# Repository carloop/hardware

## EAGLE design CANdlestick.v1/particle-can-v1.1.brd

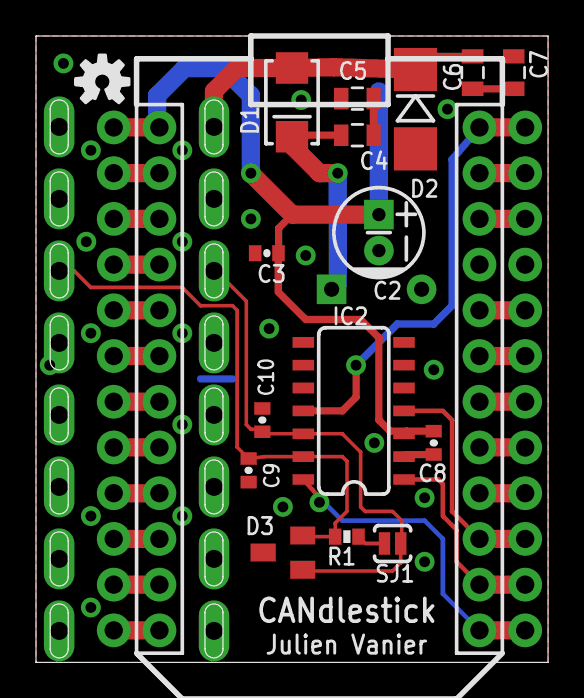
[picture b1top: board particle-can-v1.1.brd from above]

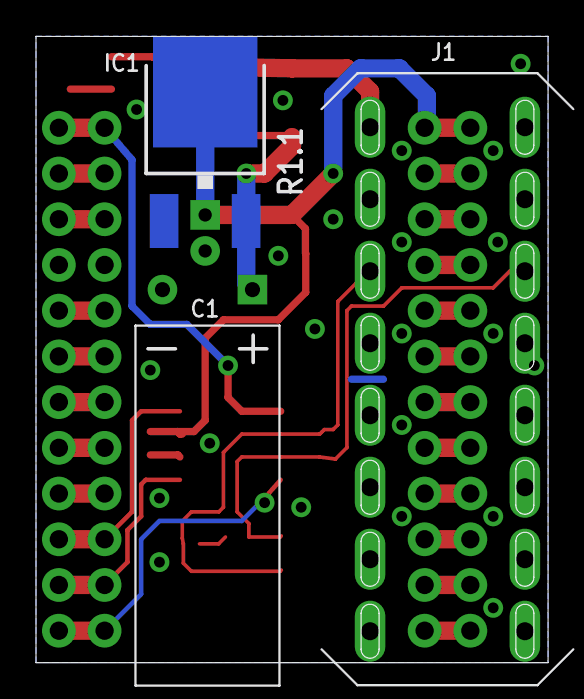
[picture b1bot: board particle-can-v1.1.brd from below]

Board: 2 copper layers, 28.4 x 34.8 mm, 22 parts (3 on the bottom side), 30 nets.

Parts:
C1: 270u; CPOL-8MMX20MM-FLAT
C2: 150u; CPOL-5MMX2D
C3: 22n; 0402-CAP
C4, C5: 0.1u; 0805
C6, C7: 0.47u; 0805
C8: 0.1u; 0402-CAP
C9, C10: 100p; 0402-CAP
CORE: SPARK_COREOUTSIDE; SPARK_CORE_OUTSIDE
D1: RS1J; SMA-DIODE
D2: 1SMB16CAT3G; SMB-DIODE
D3: PESD1CAN; SOT23
DRILEGEND: DRILEGEND
F2: OSHW-LOGO-S
IC1: LM340S-50; V-REG_DPACK
IC2: TJA1048T; SO14
J1: OBDII; OBDII-STRAIGHT
R1: 120; 0402-RES
SJ1: OPEN; SJ_2S-NO
ZDRAW1: A4L-LOC

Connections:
3.3V: CORE.24, CORE.@24, IC2.11
5V: C2.1, C3.1, C8.2, CORE.1, CORE.@1, IC1.4, IC2.3
+12V: C6.1, D1.A, D2.C, J1.16
CANA_EN: CORE.13, CORE.@13, IC2.14
CANA_RX: CORE.15, CORE.@15, IC2.4
CANA_TX: CORE.14, CORE.@14, IC2.1
GND: C1.1, C2.2, C3.2, C5.2, C7.2, C8.1, C9.2, C10.2, CORE.2, CORE.21, CORE.@2, CORE.@21, D2.A, D3.3, IC1.1, IC2.2, IC2.5, J1.4, J1.5
HSPD_HI: C9.1, D3.2, IC2.13, J1.6, R1.1
HSPD_LO: C10.1, D3.1, IC2.12, J1.14, SJ1.1
unnamed: R1.2, SJ1.2
unnamed: C6.2, C7.1
unnamed: CORE.23, CORE.@23
unnamed: CORE.22, CORE.@22
unnamed: CORE.20, CORE.@20
unnamed: CORE.19, CORE.@19
unnamed: CORE.18, CORE.@18
unnamed: CORE.17, CORE.@17
unnamed: CORE.16, CORE.@16
unnamed: CORE.12, CORE.@12
unnamed: CORE.11, CORE.@11
unnamed: CORE.10, CORE.@10
unnamed: CORE.9, CORE.@9
unnamed: C4.2, C5.1
unnamed: C1.2, C4.1, D1.C, IC1.3
unnamed: CORE.8, CORE.@8
unnamed: CORE.7, CORE.@7
unnamed: CORE.6, CORE.@6
unnamed: CORE.5, CORE.@5
unnamed: CORE.4, CORE.@4
unnamed: CORE.3, CORE.@3

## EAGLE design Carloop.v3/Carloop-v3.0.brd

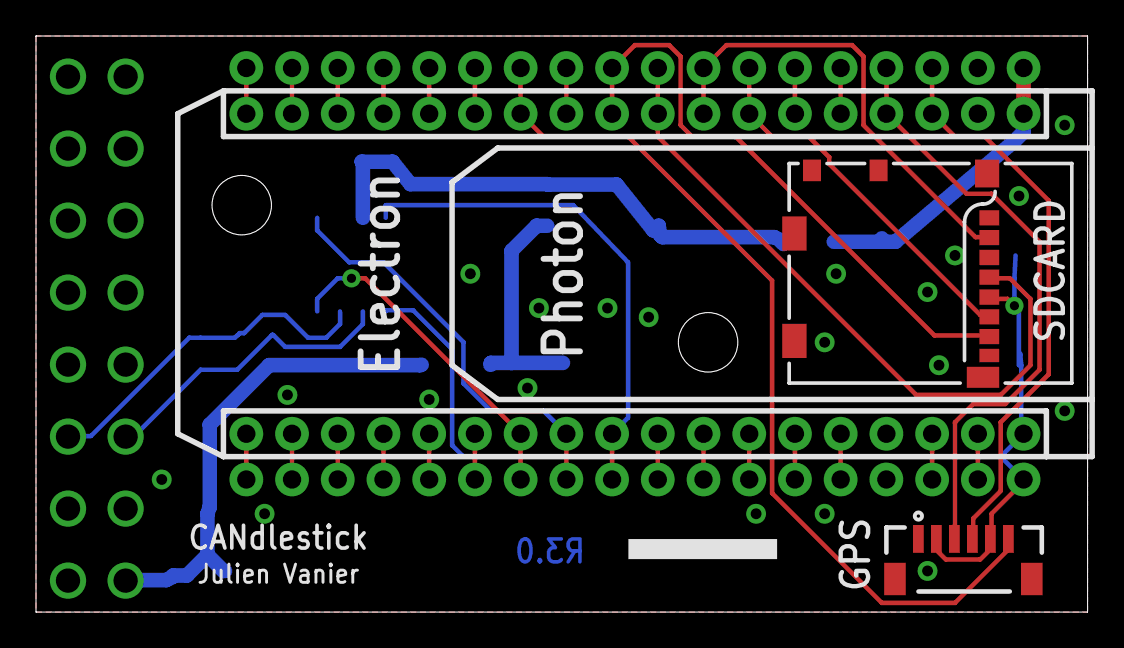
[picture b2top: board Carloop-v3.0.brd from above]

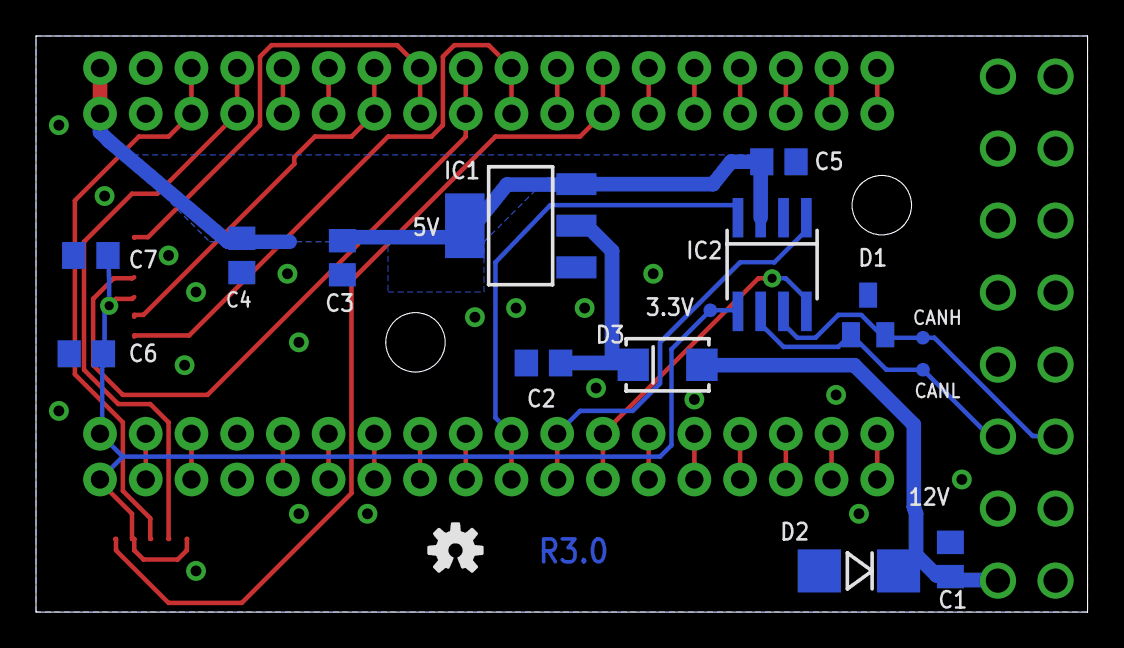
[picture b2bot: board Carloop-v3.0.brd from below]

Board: 2 copper layers, 58.4 x 32.0 mm, 24 parts (17 on the bottom side), 39 nets.

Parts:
C1: .47u; C0805
C2: 10u; C0805
C3: 22u; C0805
C4: DNP; C0805
C5, C6: 0.1u; C0805
C7: 1u; C0805
D1: PESD1CAN; SOT23
D2: 1SMB16CAT3G; SMB-DIODE
D3: RS1J; SMA-DIODE
ELECTRON: ELECTRON_WITH_EXTERNAL_HEADERS; ELECTRON_EXTERNAL
F2: OSHW-LOGO-S
GPS: JST; JST-6-SMD-VERT-1.0MM
IC1: NCP1117; SOT223
IC2: TJA1049; SO8
J1: OBDII; OBDII-COMTECH
SDCARD: USD-SOCKETMOLEX; MICRO-SD-MOLEX
STANDOFF1, STANDOFF2: STAND-OFF
TP1: CANH; PAD.03X.03
TP2: CANL; PAD.03X.03
TP3: 12V; PAD.03X.03
TP5: 3.3V; PAD.03X.03
ZDRAW1: A4L-LOC

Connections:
3.3V: C6.1, C7.1, ELECTRON.36, ELECTRON.@36, GPS.2, GPS.5, IC2.5, SDCARD.4, TP5.P$1
5V: C3.1, C4.1, C5.2, ELECTRON.1, ELECTRON.@1, IC1.3, IC1.4, IC2.3
+12V: C1.1, D2.C, D3.A, J1.16, TP3.P$1
CANA_EN: ELECTRON.25, ELECTRON.@25, IC2.8
CANA_RX: ELECTRON.27, ELECTRON.@27, IC2.4
CANA_TX: ELECTRON.26, ELECTRON.@26, IC2.1
GND: C1.2, C2.2, C3.2, C4.2, C5.1, C6.2, C7.2, D1.3, D2.A, ELECTRON.2, ELECTRON.33, ELECTRON.@2, ELECTRON.@33, GPS.1, IC1.1, IC2.2, J1.4, J1.5, SDCARD.6, SDCARD.CD1, SDCARD.CD2, SDCARD.G1, SDCARD.G2, SDCARD.G3, SDCARD.G4
GPS_EN: ELECTRON.12, ELECTRON.@12, GPS.6
GPS_RX: ELECTRON.3, ELECTRON.@3, GPS.4
GPS_TX: ELECTRON.4, ELECTRON.@4, GPS.3
HSPD_HI: D1.2, IC2.7, J1.6, TP1.P$1
HSPD_LO: D1.1, IC2.6, J1.14, TP2.P$1
unnamed: ELECTRON.13, ELECTRON.@13
unnamed: ELECTRON.14, ELECTRON.@14
unnamed: ELECTRON.35, ELECTRON.@35
unnamed: ELECTRON.34, ELECTRON.@34
unnamed: ELECTRON.32, ELECTRON.@32
unnamed: ELECTRON.31, ELECTRON.@31
unnamed: ELECTRON.30, ELECTRON.@30
unnamed: ELECTRON.29, ELECTRON.@29
unnamed: ELECTRON.28, ELECTRON.@28
unnamed: ELECTRON.15, ELECTRON.@15
unnamed: ELECTRON.11, ELECTRON.@11
unnamed: ELECTRON.16, ELECTRON.@16
unnamed: ELECTRON.17, ELECTRON.@17
unnamed: ELECTRON.18, ELECTRON.@18
unnamed: ELECTRON.19, ELECTRON.@19
unnamed: ELECTRON.20, ELECTRON.@20
unnamed: ELECTRON.21, ELECTRON.@21
unnamed: ELECTRON.6, ELECTRON.@6
unnamed: ELECTRON.5, ELECTRON.@5
unnamed: ELECTRON.23, ELECTRON.@23
unnamed: ELECTRON.24, ELECTRON.@24
unnamed: ELECTRON.22, ELECTRON.@22
unnamed: C2.1, D3.C, IC1.2
SD_CS: ELECTRON.10, ELECTRON.@10, SDCARD.2
SPI_MISO: ELECTRON.8, ELECTRON.@8, SDCARD.7
SPI_MOSI: ELECTRON.7, ELECTRON.@7, SDCARD.3
SPI_SCK: ELECTRON.9, ELECTRON.@9, SDCARD.5

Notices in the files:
parts and their libraries:
SparkFun-Passives: Licensing: CC v3.0 Share-Alike You are welcome to use this library for commercial purposes.
SparkFun-Electromechanical: Licensing: Creative Commons ShareAlike 4.0 International - https://creativecommons.org/licenses/by-sa/4.0
